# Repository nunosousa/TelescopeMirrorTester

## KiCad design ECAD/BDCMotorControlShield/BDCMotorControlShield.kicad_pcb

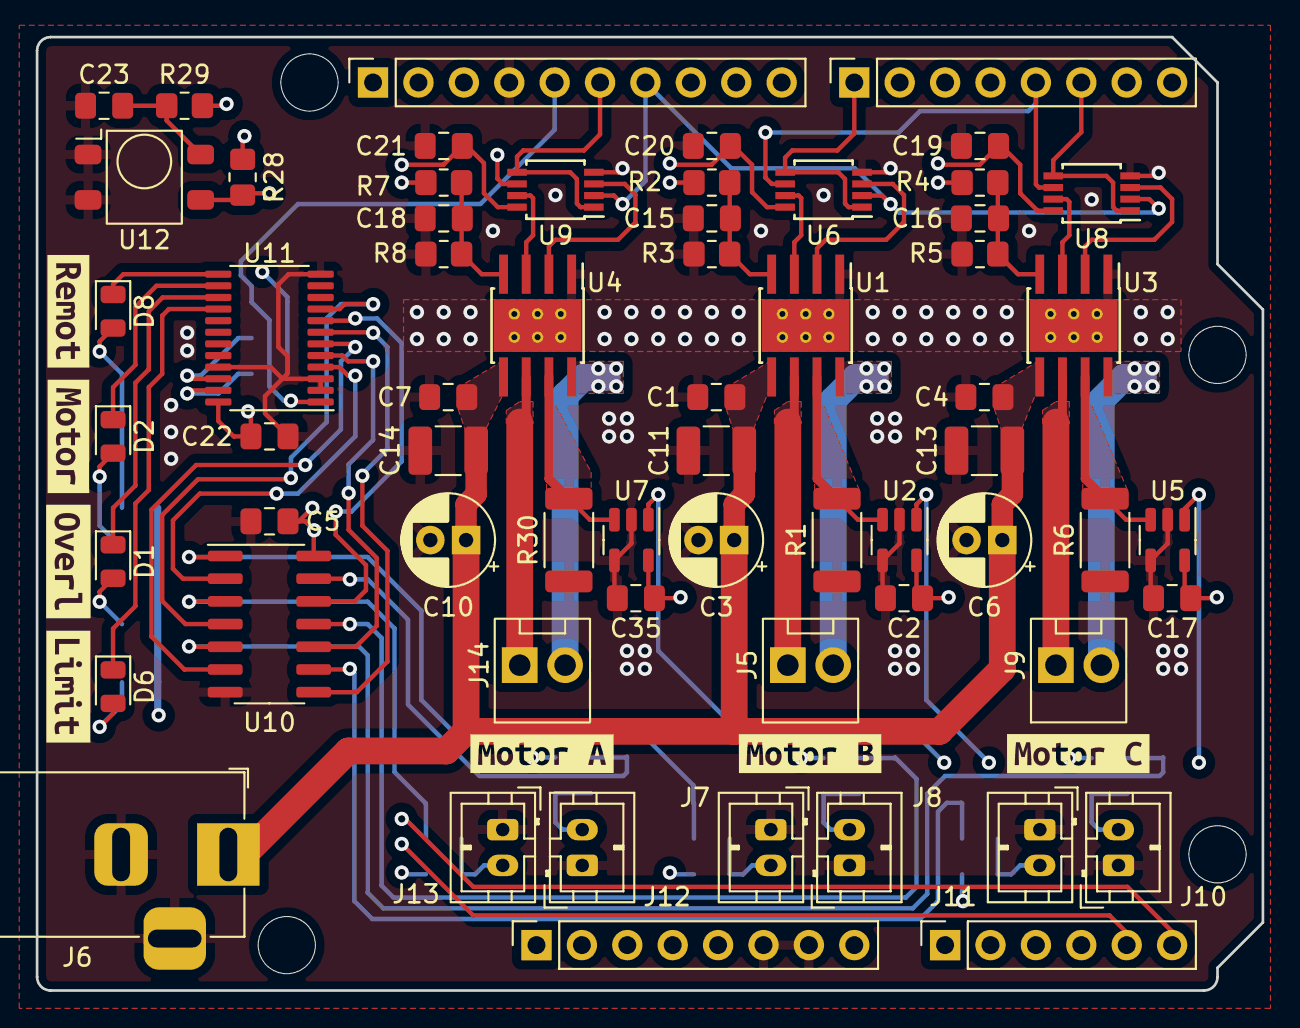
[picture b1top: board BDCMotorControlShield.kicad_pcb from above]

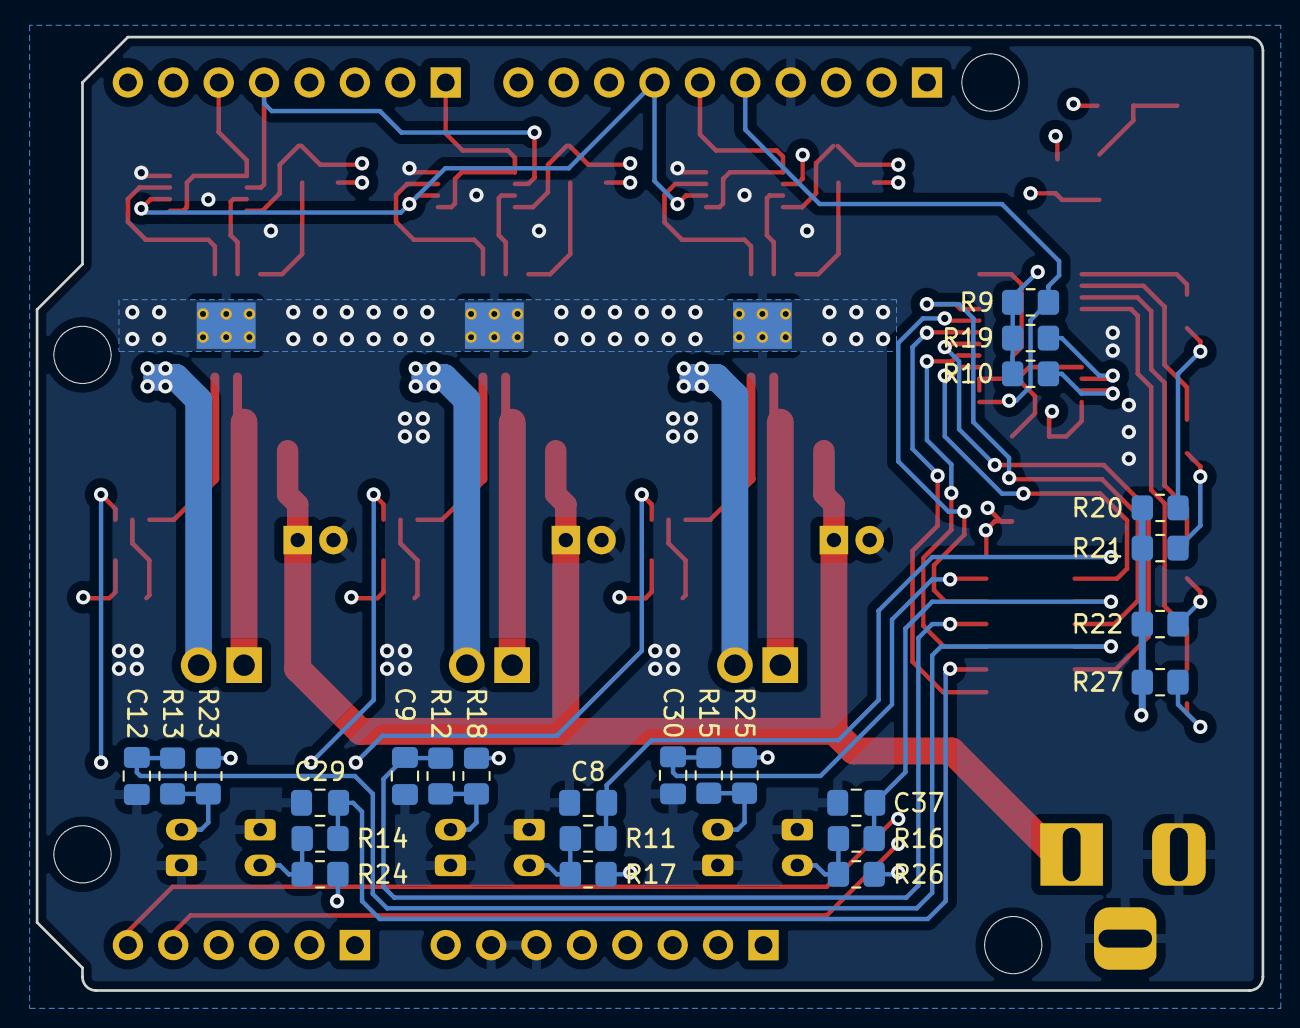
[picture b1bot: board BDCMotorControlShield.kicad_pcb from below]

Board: 4 copper layers, 68.6 x 53.3 mm, 98 parts (25 on the bottom side), 60 nets.

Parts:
C1, C2, C4, C5, C7, C8, C9, C12, C15, C16, C17, C18, C19, C20, C21, C22, C29, C30, C35, C37: 0.1uC; C_0805_2012Metric_Pad1.18x1.45mm_HandSolder
C3, C6, C10: 47uC; CP_Radial_D5.0mm_P2.00mm
C11, C13, C14: 10uC; C_1210_3225Metric_Pad1.33x2.70mm_HandSolder
C23: 4.7uC; C_0805_2012Metric_Pad1.18x1.45mm_HandSolder
D1, D2, D6, D8: LED; LED_0805_2012Metric
J1: Power; PinSocket_1x08_P2.54mm_Vertical
J2: Digital/PWM; PinSocket_1x10_P2.54mm_Vertical
J3: Analog; PinSocket_1x06_P2.54mm_Vertical
J4: Digital/PWM; PinSocket_1x08_P2.54mm_Vertical
J5, J9, J14: Motor connector; HC-2510-2A
J6: Barrel_Jack_Switch; BarrelJack_Horizontal
J7, J8, J10, J11, J12, J13: Limit switch; JST_PH_B2B-PH-K_1x02_P2.00mm_Vertical
MH1, MH2, MH3, MH4: MountingHole_3.2mm
R1, R6, R30: 250mR; R_2010_5025Metric
R2, R3, R4, R5, R7, R8, R9, R10, R11, R12, R13, R14, R15, R16, R17, R18, R19, R23, R24, R25, R26, R28: 10kR; R_0805_2012Metric_Pad1.20x1.40mm_HandSolder
R20, R21, R22, R27: 1kR; R_0805_2012Metric_Pad1.20x1.40mm_HandSolder
R29: 160R; R_0805_2012Metric_Pad1.20x1.40mm_HandSolder
U1, U3, U4: DRV8870DDA; Texas_HTSOP-8-1EP_3.9x4.9mm_P1.27mm_EP2.95x4.9mm_Mask2.4x3.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
U2, U5, U7: INA180A1; SOT-23-5
U6, U8, U9: 74HC2G08; TSSOP-8_3x3mm_P0.65mm
U10: 74HC14; SO-14_3.9x8.65mm_P1.27mm
U11: PCA9535PW; TSSOP-24_4.4x7.8mm_P0.65mm
U12: IRM-H6XX
kibuzzard-6387CFDB: G***; kibuzzard-6387CFDB
kibuzzard-6387D00C: G***; kibuzzard-6387D00C
kibuzzard-6387D004: G***; kibuzzard-6387D004
kibuzzard-6387D23A: G***; kibuzzard-6387D23A
kibuzzard-6387D063: G***; kibuzzard-6387D063
kibuzzard-6387D241: G***; kibuzzard-6387D241
kibuzzard-6387D249: G***; kibuzzard-6387D249

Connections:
+5V: C2.1, C5.1, C17.1, C19.1, C20.1, C21.1, C22.1, C35.1, J1.5, R2.1, R4.1, R7.1, R9.1, R10.1, R17.1, R18.1, R19.1, R20.1, R21.1, R22.1, R23.1, R24.1, R25.1, R26.1, R27.1, R28.1, R29.2, U2.5 (V+), U5.5 (V+), U6.8 (VCC), U7.5 (V+), U8.8 (VCC), U9.8 (VCC), U10.14 (VCC), U11.24 (VDD)
+12V: C1.1, C3.1, C4.1, C6.1, C7.1, C10.1, C11.1, C13.1, C14.1, J6.1, U1.5 (VM), U3.5 (VM), U4.5 (VM)
/2: J4.6, U8.1, U8.5
/7: J4.1, U6.1, U6.5
/8: J2.10, R28.2, U12.3 (OUT)
/12: J2.6, U9.1, U9.5
/13: J2.5, R9.2, U11.1 (~INT)
/*3: J4.5, U6.6, U8.6, U9.6
/*11: J2.7, U6.2, U8.2, U9.2
/A0: J3.1, U7.1
/A1: J3.2, U2.1
/A2: J3.3, U5.1
/H-bridge #1/PWM1: U1.3 (IN1), U6.7
/H-bridge #1/PWM2: U1.2 (IN2), U6.3
/H-bridge #2/PWM1: U3.3 (IN1), U8.7
/H-bridge #2/PWM2: U3.2 (IN2), U8.3
/H-bridge #3/PWM1: U4.3 (IN1), U9.7
/H-bridge #3/PWM2: U4.2 (IN2), U9.3
/LED00: D8.1 (K), U11.13 (IO1_0)
/LED01: D2.1 (K), U11.14 (IO1_1)
/LED02: D1.1 (K), U11.15 (IO1_2)
/LED03: D6.1 (K), U11.16 (IO1_3)
/LIM_SW00: U10.2, U11.4 (IO0_0)
/LIM_SW01: U10.10, U11.5 (IO0_1)
/LIM_SW02: U10.6, U11.6 (IO0_2)
/LIM_SW03: U10.8, U11.7 (IO0_3)
/LIM_SW04: U10.12, U11.8 (IO0_4)
/LIM_SW05: U10.4, U11.9 (IO0_5)
/SCL/A5: J2.1, J3.6, R19.2, U11.22 (SCL)
/SDA/A4: J2.2, J3.5, R10.2, U11.23 (SDA)
GND: C1.2, C2.2, C3.2, C4.2, C5.2, C6.2, C7.2, C8.2, C9.2, C10.2, C11.2, C12.2, C13.2, C14.2, C15.2, C16.2, C17.2, C18.2, C19.2, C20.2, C21.2, C22.2, C23.2, C29.2, C30.2, C35.2, C37.2, J1.6, J1.7, J2.4, J6.2, J6.3, J7.1, J8.1, J10.1, J11.1, J12.1, J13.1, R1.1, R3.2, R5.2, R6.1, R8.2, R30.1, U1.1 (GND), U1.9 (GND), U2.2 (GND), U2.4 (-), U3.1 (GND), U3.9 (GND), U4.1 (GND), U4.9 (GND), U5.2 (GND), U5.4 (-), U6.4 (GND), U7.2 (GND), U7.4 (-), U8.4 (GND), U9.4 (GND), U10.7 (GND), U11.2 (A1), U11.3 (A2), U11.12 (VSS), U11.21 (A0), U12.1 (GND), U12.2 (GND)
unnamed: C8.1, R11.2, U10.1
unnamed: C9.1, R12.2, U10.11
unnamed: C12.1, R13.2, U10.5
unnamed: C15.1, R2.2, R3.1, U1.4 (VREF)
unnamed: C16.1, R4.2, R5.1, U3.4 (VREF)
unnamed: C18.1, R7.2, R8.1, U4.4 (VREF)
unnamed: C23.1, R29.1, U12.4 (Vs)
unnamed: C29.1, R14.2, U10.9
unnamed: C30.1, R15.2, U10.13
unnamed: C37.1, R16.2, U10.3
unnamed: D1.2 (A), R22.2
unnamed: D2.2 (A), R21.2
unnamed: D6.2 (A), R27.2
unnamed: D8.2 (A), R20.2
unnamed: J5.1, U1.6 (OUT1)
unnamed: J5.2, U1.8 (OUT2)
unnamed: J7.2, R11.1, R17.2
unnamed: J8.2, R12.1, R18.2
unnamed: J9.1, U3.6 (OUT1)
unnamed: J9.2, U3.8 (OUT2)
unnamed: J10.2, R13.1, R23.2
unnamed: J11.2, R14.1, R24.2
unnamed: J12.2, R15.1, R25.2
unnamed: J13.2, R16.1, R26.2
unnamed: J14.1, U4.6 (OUT1)
unnamed: J14.2, U4.8 (OUT2)
unnamed: R1.2, U1.7 (ISEN), U2.3 (+)
unnamed: R6.2, U3.7 (ISEN), U5.3 (+)
unnamed: R30.2, U4.7 (ISEN), U7.3 (+)

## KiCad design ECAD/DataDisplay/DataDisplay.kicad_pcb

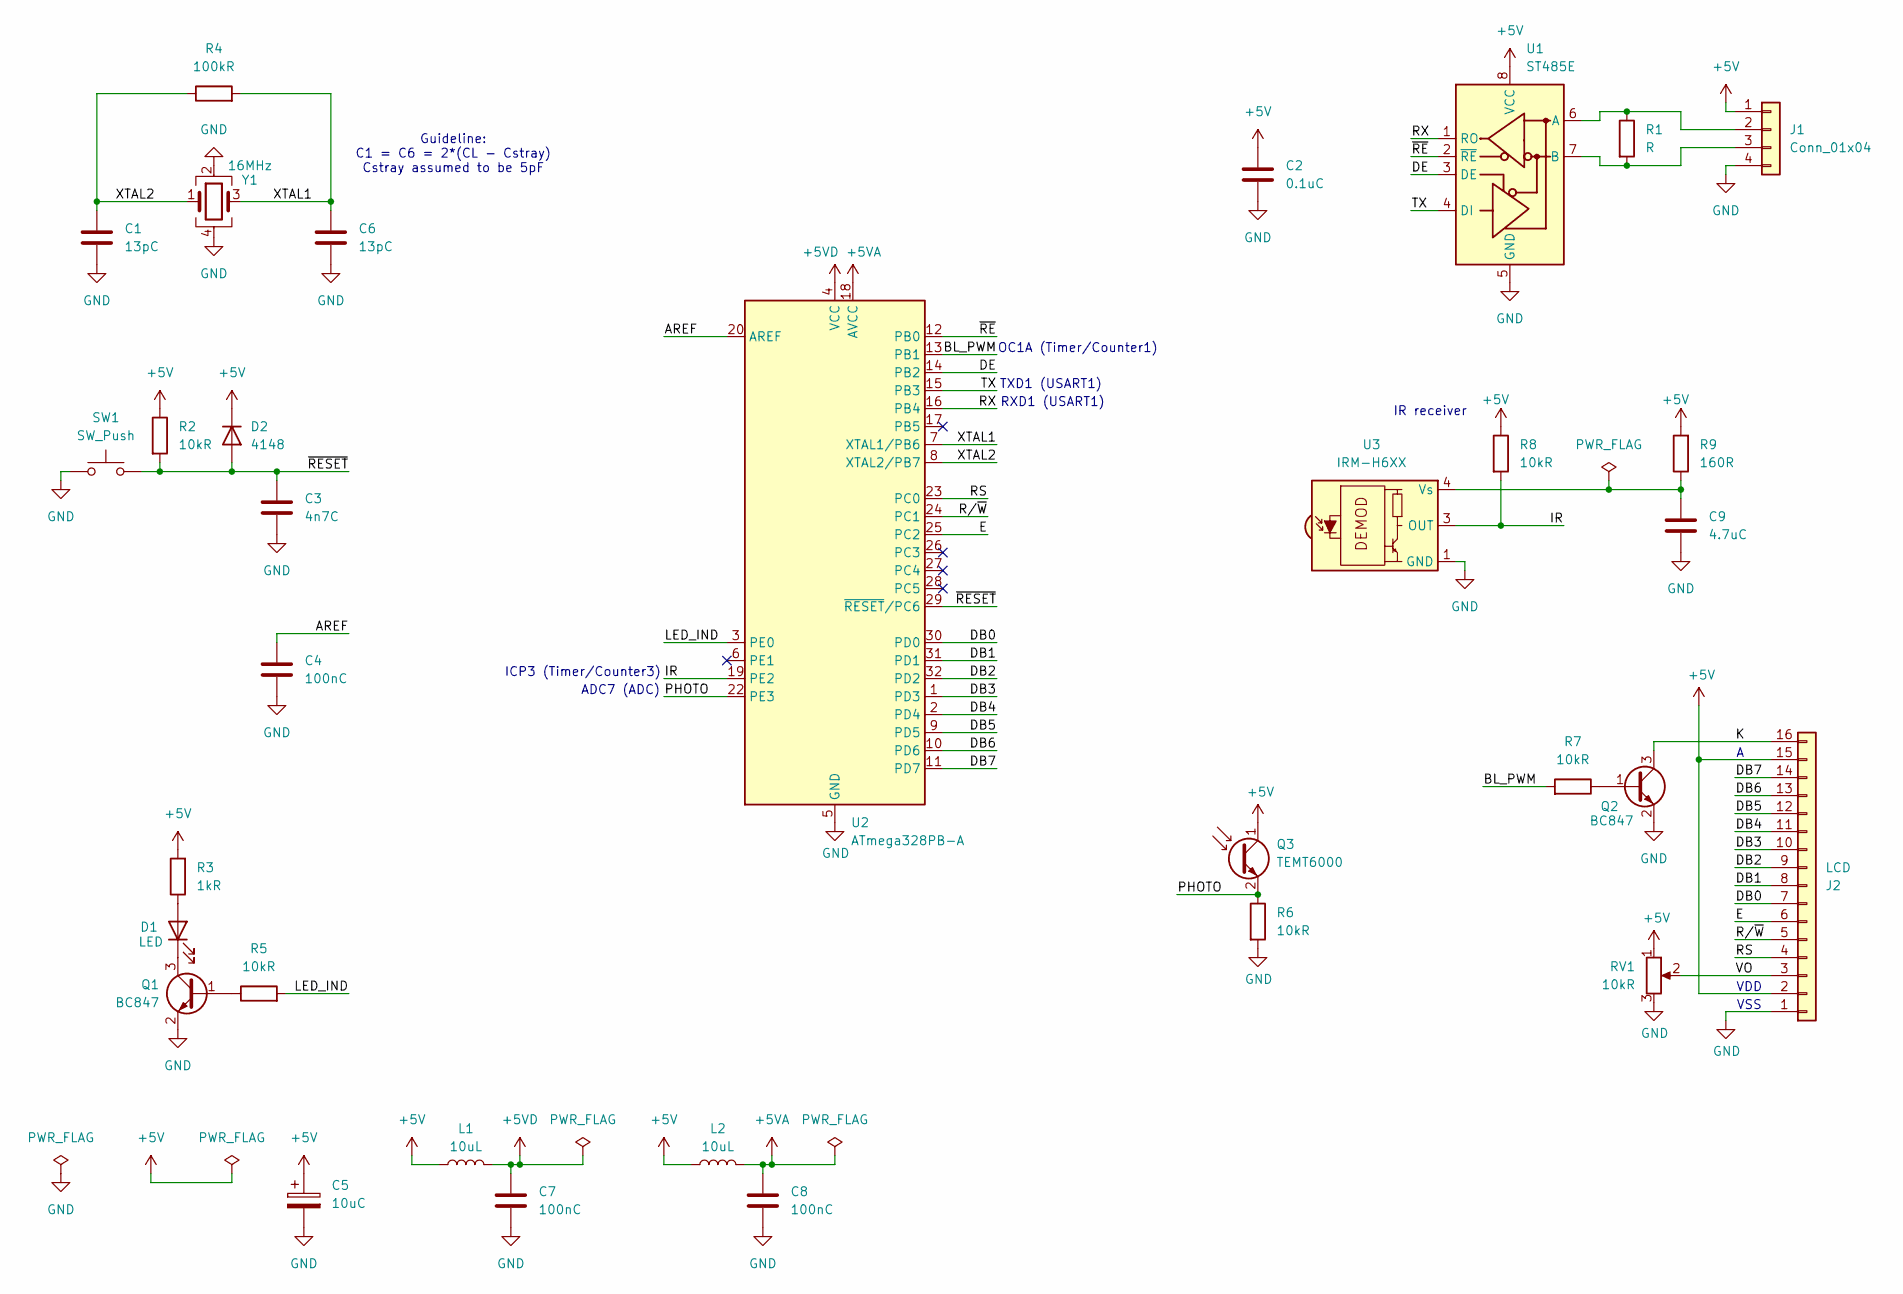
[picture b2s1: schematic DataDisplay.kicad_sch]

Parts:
C1, C6: 13pC; C_0805_2012Metric
C2: 0.1uC; C_0805_2012Metric
C3: 4n7C; C_0805_2012Metric
C4, C7, C8: 100nC; C_0805_2012Metric
C5: 10uC; CP_Elec_4x5.4; MPN UWX1C100MCL1GB
C9: 4.7uC; C_0805_2012Metric_Pad1.18x1.45mm_HandSolder; MPN CC0805KKX7R8BB475
D1: LED; LED_0805_2012Metric; MPN LTST-C171KGKT
D2: 4148; D_SOD-123; MPN MMSD4148T1G
J1: Conn_01x04; JST_EH_B4B-EH-A_1x04_P2.50mm_Vertical
J2: LCD; PinHeader_1x16_P2.54mm_Vertical
L1, L2: 10uL; L_0805_2012Metric; MPN LQM21FN100M80L
Q1, Q2: BC847; SOT-23; MPN BC847C,215
Q3: TEMT6000; MPN TEMT6000X01
R1: R
R2, R5, R6, R7: 10kR; R_0805_2012Metric
R3: 1kR; R_0805_2012Metric
R4: 100kR; R_0805_2012Metric
R8: 10kR; R_0805_2012Metric; MPN RC0805FR-0710KL
R9: 160R; R_0805_2012Metric_Pad1.20x1.40mm_HandSolder; MPN AC0805FR-7W160RL
RV1: 10kR
SW1: SW_Push; SW_Push_1P1T_XKB_TS-1187A; MPN TS-1187A-C-E-B
U1: ST485E; SOIC-8_3.9x4.9mm_P1.27mm; MPN ST485EBDR
U2: ATmega328PB-A; TQFP-32_7x7mm_P0.8mm
U3: IRM-H6XX; MPN IRM-H638J7/TR2(CLW)
Y1: 16MHz; Crystal_SMD_3225-4Pin_3.2x2.5mm; MPN X1E0000210119

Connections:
+5V: C2.1, C5.1, D2.1 (K), J1.1, J2.2, J2.15, L1.1, L2.1, Q3.1 (C), R2.1, R3.2, R8.1, R9.2, RV1.1, U1.8 (VCC)
+5VA: C8.1, L2.2, U2.18 (AVCC)
+5VD: C7.1, L1.2, U2.4 (VCC)
/AREF: C4.1, U2.20 (AREF)
/BL_PWM: R7.2, U2.13 (PB1)
/DB0: J2.7, U2.30 (PD0)
/DB1: J2.8, U2.31 (PD1)
/DB2: J2.9, U2.32 (PD2)
/DB3: J2.10, U2.1 (PD3)
/DB4: J2.11, U2.2 (PD4)
/DB5: J2.12, U2.9 (PD5)
/DB6: J2.13, U2.10 (PD6)
/DB7: J2.14, U2.11 (PD7)
/DE: U1.3 (DE), U2.14 (PB2)
/E: J2.6, U2.25 (PC2)
/IR: R8.2, U2.19 (PE2), U3.3 (OUT)
/K: J2.16, Q2.3 (C)
/LED_IND: R5.2, U2.3 (PE0)
/PHOTO: Q3.2 (E), R6.1, U2.22 (PE3)
/RS: J2.4, U2.23 (PC0)
/RX: U1.1 (RO), U2.16 (PB4)
/R/~W: J2.5, U2.24 (PC1)
/TX: U1.4 (DI), U2.15 (PB3)
/VO: J2.3, RV1.2
/XTAL1: C6.1, R4.2, U2.7 (XTAL1/PB6), Y1.3
/XTAL2: C1.1, R4.1, U2.8 (XTAL2/PB7), Y1.1
/~RESET: C3.1, D2.2 (A), R2.2, SW1.2, U2.29 (~RESET/PC6)
/~RE: U1.2 (~RE), U2.12 (PB0)
GND: C1.2, C2.2, C3.2, C4.2, C5.2, C6.2, C7.2, C8.2, C9.2, J1.4, J2.1, Q1.2 (E), Q2.2 (E), R6.2, RV1.3, SW1.1, U1.5 (GND), U2.5 (GND), U2.21 (GND), U3.1 (GND), U3.2 (GND), Y1.2, Y1.4
unnamed: D1.2 (A), R3.1
unnamed: D1.1 (K), Q1.3 (C)
unnamed: J1.2, R1.1, U1.6 (A)
unnamed: J1.3, R1.2, U1.7 (B)
unnamed: Q1.1 (B), R5.1
unnamed: Q2.1 (B), R7.1
unnamed: C9.1, R9.1, U3.4 (Vs)

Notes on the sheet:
TXD1 (USART1)
Guideline: C1 = C6 = 2*(CL - Cstray) Cstray assumed to be 5pF
IR receiver
ICP3 (Timer/Counter3)
ADC7 (ADC)
VSS
OC1A (Timer/Counter1)
VDD
RXD1 (USART1)

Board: 2 copper layers, 30 parts (0 on the bottom side), 35 nets, no tracks yet.

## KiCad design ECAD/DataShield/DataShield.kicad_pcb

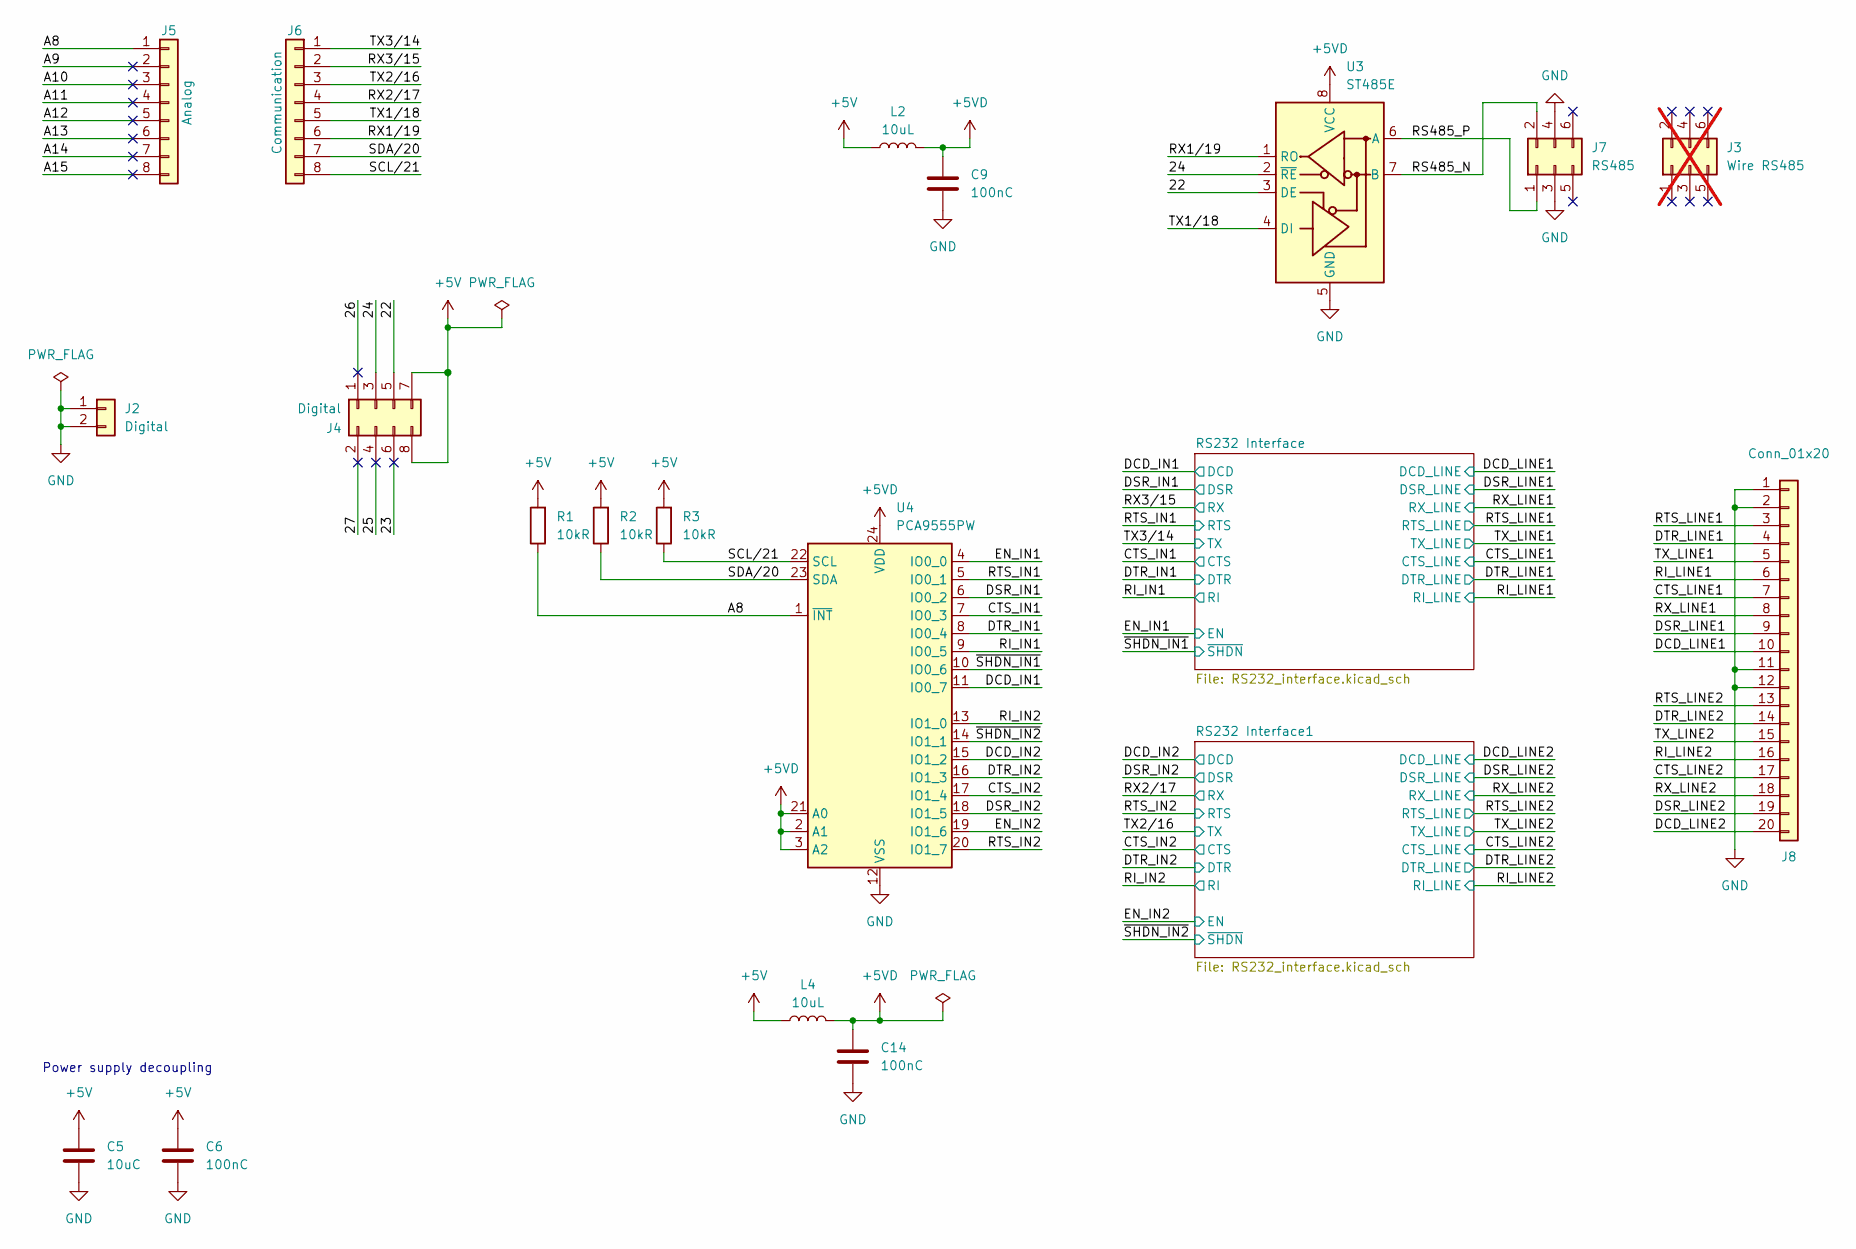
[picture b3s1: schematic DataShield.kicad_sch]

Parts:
C5: 10uC; C_1206_3216Metric; MPN CL31B106KOHNNNE
C6, C9, C14: 100nC; C_0805_2012Metric; MPN C0805F104K5RACAUTO
J2: Digital; PinSocket_1x02_P2.54mm_Vertical; MPN PM254-1-02-Z-8.5
J3: Wire RS485; IDC-Header_2x03_P2.54mm_Vertical; MPN I254-2*3-G-3-B; not fitted
J4: Digital; PinSocket_2x04_P2.54mm_Vertical; MPN PM254-2-04-Z-8.5
J5: Analog; PinSocket_1x08_P2.54mm_Vertical; MPN PZ254-1-08-Z-8.5
J6: Communication; PinSocket_1x08_P2.54mm_Vertical; MPN PZ254-1-08-Z-8.5
J7: RS485; IDC-Header_2x03_P2.54mm_Vertical; MPN HC-JN254-2-03-Z
J8: Conn_01x20; TE_2-84952-0_1x20-1MP_P1.0mm_Horizontal; MPN CT10252-20R-00-D
L2, L4: 10uL; L_0805_2012Metric; MPN LQM21FN100M80L
R1, R2, R3: 10kR; R_0805_2012Metric; MPN RC0805JR-0710KL
U3: ST485E; SOIC-8_3.9x4.9mm_P1.27mm; MPN ST485EBDR
U4: PCA9555PW; TSSOP-24_4.4x7.8mm_P0.65mm; MPN PCA9555PW,118

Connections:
+5V: C5.1, C6.1, J4.7, J4.8, L2.1, L4.1, R1.2, R2.2, R3.2; also elsewhere on the board
+5VD: C9.1, C14.1, L2.2, L4.2, U3.8 (VCC), U4.2 (A1), U4.3 (A2), U4.21 (A0), U4.24 (VDD); also elsewhere on the board
/22: J4.5, U3.3 (DE)
/23: J4.6
/24: J4.3, U3.2 (~RE)
/25: J4.4
/26: J4.1
/27: J4.2
/A8: J5.1, R1.1, U4.1 (~INT)
/A9: J5.2
/A10: J5.3
/A11: J5.4
/A12: J5.5
/A13: J5.6
/A14: J5.7
/A15: J5.8
/CTS_IN1: U4.7 (IO0_3); also elsewhere on the board
/CTS_IN2: U4.17 (IO1_4); also elsewhere on the board
/CTS_LINE1: J8.7; also elsewhere on the board
/CTS_LINE2: J8.17; also elsewhere on the board
/DCD_IN1: U4.11 (IO0_7); also elsewhere on the board
/DCD_IN2: U4.15 (IO1_2); also elsewhere on the board
/DCD_LINE1: J8.10; also elsewhere on the board
/DCD_LINE2: J8.20; also elsewhere on the board
/DSR_IN1: U4.6 (IO0_2); also elsewhere on the board
/DSR_IN2: U4.18 (IO1_5); also elsewhere on the board
/DSR_LINE1: J8.9; also elsewhere on the board
/DSR_LINE2: J8.19; also elsewhere on the board
/DTR_IN1: U4.8 (IO0_4); also elsewhere on the board
/DTR_IN2: U4.16 (IO1_3); also elsewhere on the board
/DTR_LINE1: J8.4; also elsewhere on the board
/DTR_LINE2: J8.14; also elsewhere on the board
/EN_IN1: U4.4 (IO0_0); also elsewhere on the board
/EN_IN2: U4.19 (IO1_6); also elsewhere on the board
/RI_IN1: U4.9 (IO0_5); also elsewhere on the board
/RI_IN2: U4.13 (IO1_0); also elsewhere on the board
/RI_LINE1: J8.6; also elsewhere on the board
/RI_LINE2: J8.16; also elsewhere on the board
/RS485_N: J7.2, U3.7 (B)
/RS485_P: J7.1, U3.6 (A)
/RTS_IN1: U4.5 (IO0_1); also elsewhere on the board
/RTS_IN2: U4.20 (IO1_7); also elsewhere on the board
/RTS_LINE1: J8.3; also elsewhere on the board
/RTS_LINE2: J8.13; also elsewhere on the board
/RX1/19: J6.6, U3.1 (RO)
/RX2/17: J6.4; also elsewhere on the board
/RX3/15: J6.2; also elsewhere on the board
/RX_LINE1: J8.8; also elsewhere on the board
/RX_LINE2: J8.18; also elsewhere on the board
/SCL/21: J6.8, R3.1, U4.22 (SCL)
/SDA/20: J6.7, R2.1, U4.23 (SDA)
/TX1/18: J6.5, U3.4 (DI)
/TX2/16: J6.3; also elsewhere on the board
/TX3/14: J6.1; also elsewhere on the board
/TX_LINE1: J8.5; also elsewhere on the board
/TX_LINE2: J8.15; also elsewhere on the board
/~SHDN_IN1: U4.10 (IO0_6); also elsewhere on the board
/~SHDN_IN2: U4.14 (IO1_1); also elsewhere on the board
GND: C5.2, C6.2, C9.2, C14.2, J2.1, J2.2, J7.3, J7.4, J8.1, J8.2, J8.11, J8.12, U3.5 (GND), U4.12 (VSS); also elsewhere on the board

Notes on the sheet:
Power supply decoupling

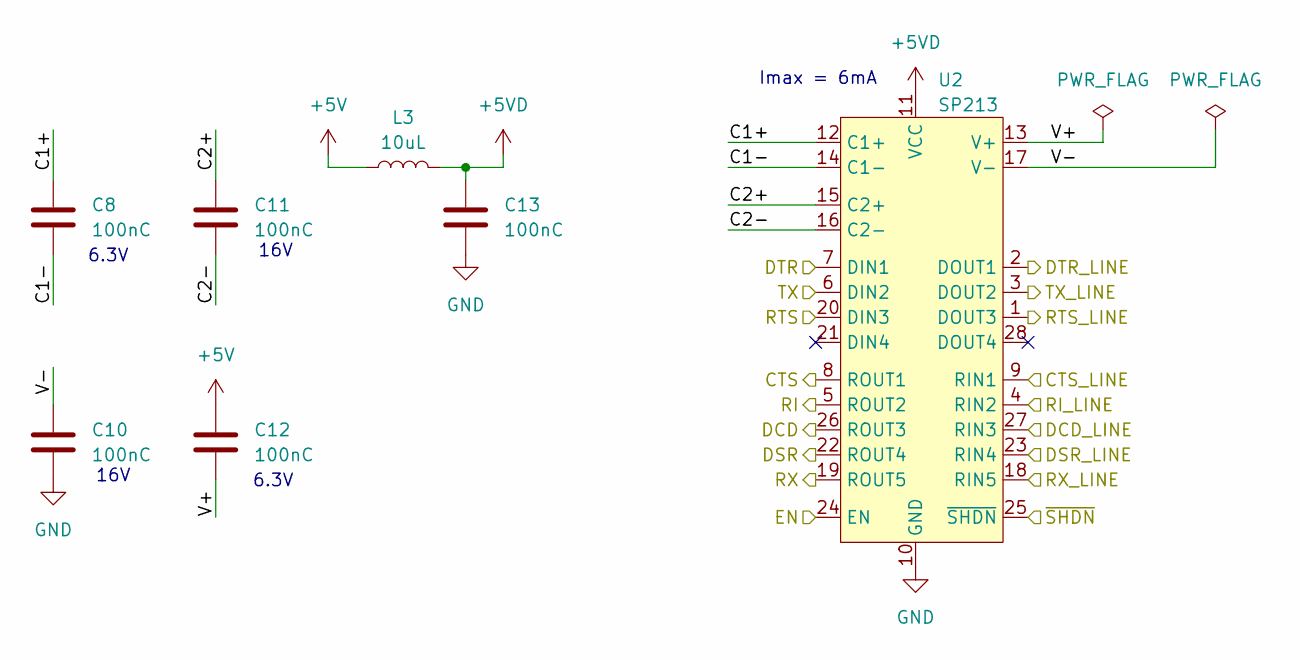
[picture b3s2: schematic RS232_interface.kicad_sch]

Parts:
C8, C10, C11, C12, C13: 100nC; C_0805_2012Metric; MPN C0805F104K5RACAUTO
L3: 10uL; L_0805_2012Metric; MPN LQM21FN100M80L
U2: SP213; SSOP-28_5.3x10.2mm_P0.65mm; MPN SP213EEA-L/TR

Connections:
+5V: C12.1, L3.1; also elsewhere on the board
+5VD: C13.1, L3.2, U2.11 (VCC); also elsewhere on the board
/CTS_IN2: U2.8 (ROUT1); also elsewhere on the board
/CTS_LINE2: U2.9 (RIN1); also elsewhere on the board
/DCD_IN2: U2.26 (ROUT3); also elsewhere on the board
/DCD_LINE2: U2.27 (RIN3); also elsewhere on the board
/DSR_IN2: U2.22 (ROUT4); also elsewhere on the board
/DSR_LINE2: U2.23 (RIN4); also elsewhere on the board
/DTR_IN2: U2.7 (DIN1); also elsewhere on the board
/DTR_LINE2: U2.2 (DOUT1); also elsewhere on the board
/EN_IN2: U2.24 (EN); also elsewhere on the board
/RI_IN2: U2.5 (ROUT2); also elsewhere on the board
/RI_LINE2: U2.4 (RIN2); also elsewhere on the board
/RS232 Interface1/C1+: C8.1, U2.12 (C1+)
/RS232 Interface1/C1-: C8.2, U2.14 (C1-)
/RS232 Interface1/C2+: C11.1, U2.15 (C2+)
/RS232 Interface1/C2-: C11.2, U2.16 (C2-)
/RS232 Interface1/V+: C12.2, U2.13 (V+)
/RS232 Interface1/V-: C10.1, U2.17 (V-)
/RTS_IN2: U2.20 (DIN3); also elsewhere on the board
/RTS_LINE2: U2.1 (DOUT3); also elsewhere on the board
/RX2/17: U2.19 (ROUT5); also elsewhere on the board
/RX_LINE2: U2.18 (RIN5); also elsewhere on the board
/TX2/16: U2.6 (DIN2); also elsewhere on the board
/TX_LINE2: U2.3 (DOUT2); also elsewhere on the board
/~SHDN_IN2: U2.25 (~SHDN); also elsewhere on the board
GND: C10.2, C13.2, U2.10 (GND); also elsewhere on the board

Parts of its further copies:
C1, C2, C3, C4, C7: 100nC; C_0805_2012Metric; MPN C0805F104K5RACAUTO
L1: 10uL; L_0805_2012Metric; MPN LQM21FN100M80L
U1: SP213; SSOP-28_5.3x10.2mm_P0.65mm; MPN SP213EEA-L/TR

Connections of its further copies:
+5V: C4.1, L1.1; also elsewhere on the board
+5VD: C7.1, L1.2, U1.11 (VCC); also elsewhere on the board
/CTS_IN1: U1.8 (ROUT1); also elsewhere on the board
/CTS_LINE1: U1.9 (RIN1); also elsewhere on the board
/DCD_IN1: U1.26 (ROUT3); also elsewhere on the board
/DCD_LINE1: U1.27 (RIN3); also elsewhere on the board
/DSR_IN1: U1.22 (ROUT4); also elsewhere on the board
/DSR_LINE1: U1.23 (RIN4); also elsewhere on the board
/DTR_IN1: U1.7 (DIN1); also elsewhere on the board
/DTR_LINE1: U1.2 (DOUT1); also elsewhere on the board
/EN_IN1: U1.24 (EN); also elsewhere on the board
/RI_IN1: U1.5 (ROUT2); also elsewhere on the board
/RI_LINE1: U1.4 (RIN2); also elsewhere on the board
/RS232 Interface/C1+: C1.1, U1.12 (C1+)
/RS232 Interface/C1-: C1.2, U1.14 (C1-)
/RS232 Interface/C2+: C3.1, U1.15 (C2+)
/RS232 Interface/C2-: C3.2, U1.16 (C2-)
/RS232 Interface/V+: C4.2, U1.13 (V+)
/RS232 Interface/V-: C2.1, U1.17 (V-)
/RTS_IN1: U1.20 (DIN3); also elsewhere on the board
/RTS_LINE1: U1.1 (DOUT3); also elsewhere on the board
/RX3/15: U1.19 (ROUT5); also elsewhere on the board
/RX_LINE1: U1.18 (RIN5); also elsewhere on the board
/TX3/14: U1.6 (DIN2); also elsewhere on the board
/TX_LINE1: U1.3 (DOUT2); also elsewhere on the board
/~SHDN_IN1: U1.25 (~SHDN); also elsewhere on the board
GND: C2.2, C7.2, U1.10 (GND); also elsewhere on the board

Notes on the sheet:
16V
Imax = 6mA
6.3V

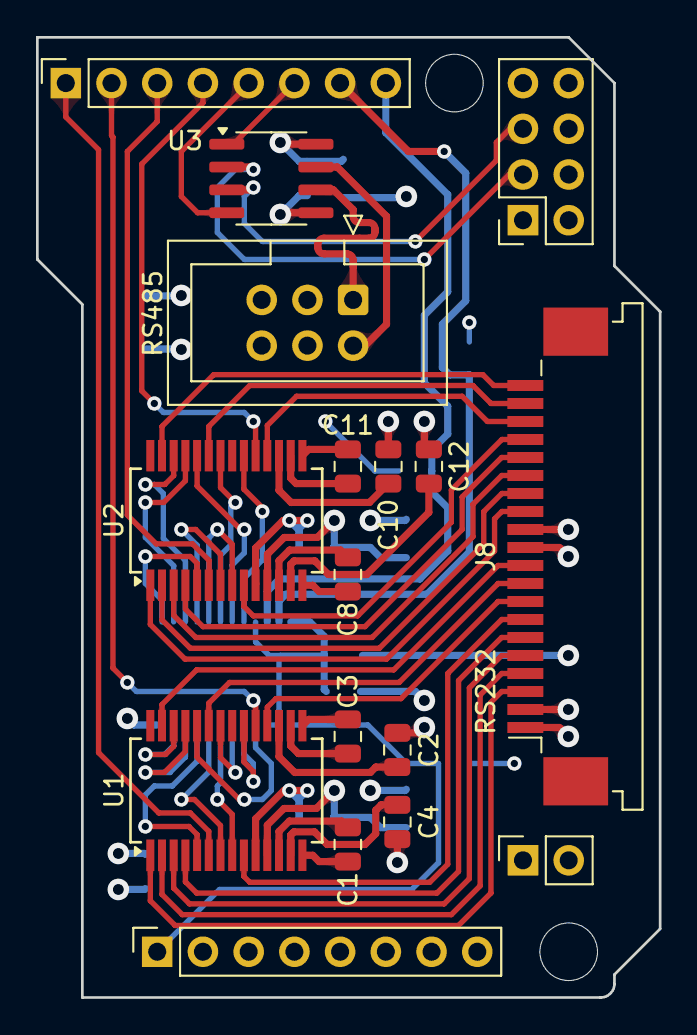
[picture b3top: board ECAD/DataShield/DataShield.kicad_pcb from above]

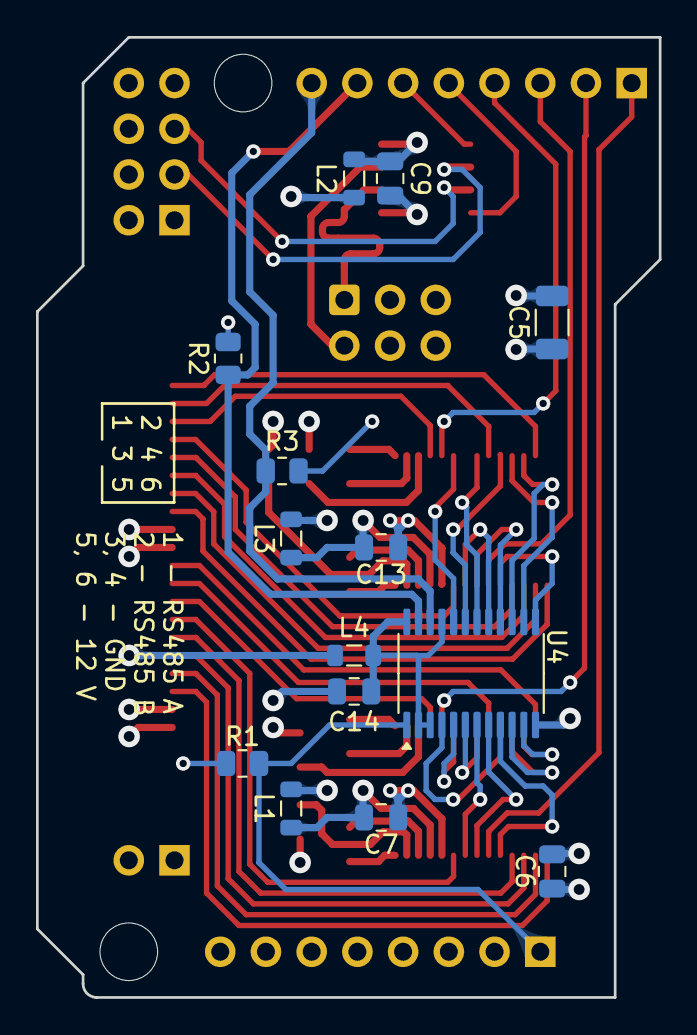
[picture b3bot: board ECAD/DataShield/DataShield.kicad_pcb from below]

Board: 4 copper layers, 34.6 x 53.3 mm, 33 parts (14 on the bottom side), 60 nets.

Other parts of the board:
MH5, MH6: MountingHole_3.2mm

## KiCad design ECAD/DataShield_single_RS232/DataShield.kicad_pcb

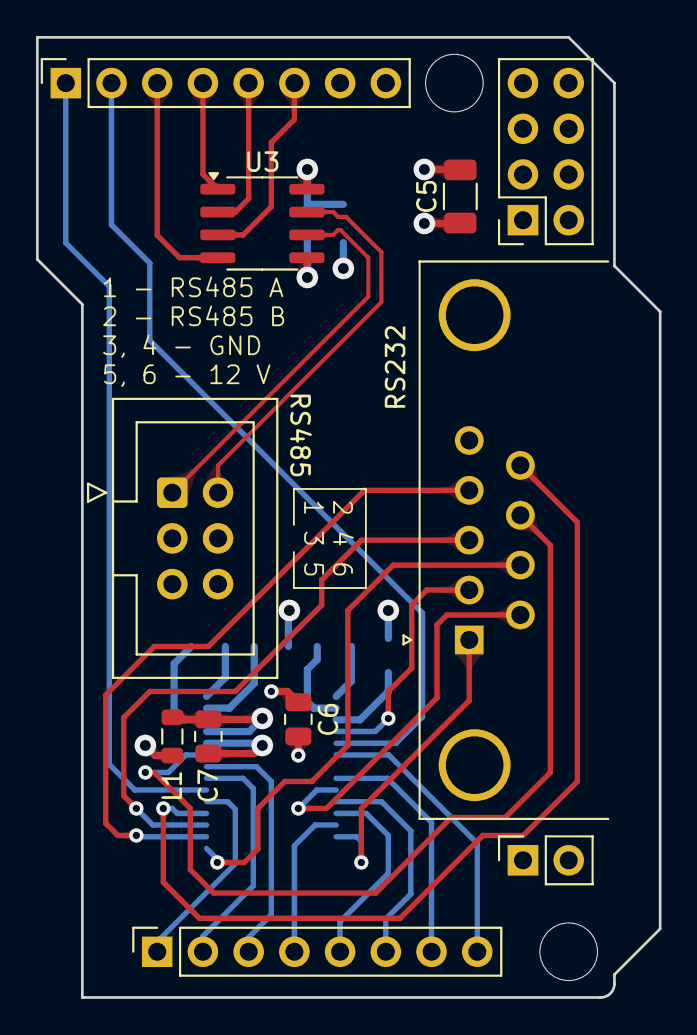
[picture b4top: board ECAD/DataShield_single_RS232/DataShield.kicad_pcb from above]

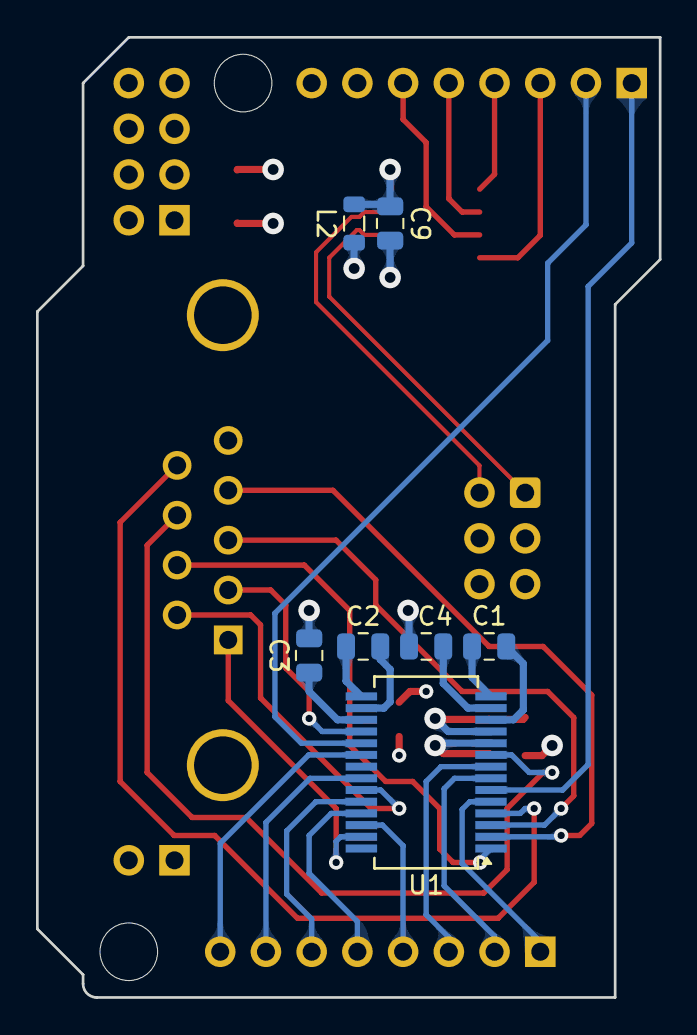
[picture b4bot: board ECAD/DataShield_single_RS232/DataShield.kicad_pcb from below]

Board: 4 copper layers, 34.6 x 53.3 mm, 20 parts (7 on the bottom side), 33 nets.

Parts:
C1, C2, C3, C4, C6, C7, C9: 100nC; C_0805_2012Metric
C5: 10uC; C_1206_3216Metric
J1: RS232; DSUB-9_Male_Horizontal_P2.77x2.84mm_EdgePinOffset4.94mm_Hou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
J2: Digital; PinSocket_1x02_P2.54mm_Vertical
J4: Digital; PinSocket_2x04_P2.54mm_Vertical
J5: Analog; PinSocket_1x08_P2.54mm_Vertical
J6: Communication; PinSocket_1x08_P2.54mm_Vertical
J7: RS485; IDC-Header_2x03_P2.54mm_Vertical
L1, L2: 10uL; L_0805_2012Metric
MH5, MH6: MountingHole_3.2mm
U1: SP213; SSOP-28_5.3x10.2mm_P0.65mm
U3: ST485E; SOIC-8_3.9x4.9mm_P1.27mm

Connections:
+5V: C4.1, C5.1, C6.1, J4.7, J4.8, L1.1, L2.1
+5VD: C7.1, C9.1, L1.2, L2.2, U1.11 (VCC), U3.8 (VCC)
/A8: J5.1, U1.5 (ROUT2)
/A9: J5.2, U1.7 (DIN1)
/A10: J5.3, U1.8 (ROUT1)
/A11: J5.4, U1.26 (ROUT3)
/A12: J5.5, U1.25 (~SHDN)
/A13: J5.6, U1.24 (EN)
/A14: J5.7, U1.22 (ROUT4)
/A15: J5.8, U1.20 (DIN3)
/C1+: C1.1, U1.12 (C1+)
/C1-: C1.2, U1.14 (C1-)
/C2+: C2.1, U1.15 (C2+)
/C2-: C2.2, U1.16 (C2-)
/CTS: J1.8, U1.9 (RIN1)
/DCD: J1.1, U1.27 (RIN3)
/DSR: J1.6, U1.23 (RIN4)
/DTR: J1.4, U1.2 (DOUT1)
/RI: J1.9, U1.4 (RIN2)
/RS485_N: J7.2, U3.7 (B)
/RS485_P: J7.1, U3.6 (A)
/RTS: J1.7, U1.1 (DOUT3)
/RX: J1.2, U1.18 (RIN5)
/RX1/19: J6.6, U3.3 (DE)
/RX2/17: J6.4, U3.1 (RO)
/RX3/15: J6.2, U1.19 (ROUT5)
/TX: J1.3, U1.3 (DOUT2)
/TX1/18: J6.5, U3.2 (~RE)
/TX2/16: J6.3, U3.4 (DI)
/TX3/14: J6.1, U1.6 (DIN2)
/V+: C4.2, U1.13 (V+)
/V-: C3.1, U1.17 (V-)
GND: C3.2, C5.2, C6.2, C7.2, C9.2, J1.5, J2.1, J2.2, J7.3, J7.4, U1.10 (GND), U3.5 (GND)
